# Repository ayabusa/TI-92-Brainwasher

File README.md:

# TI-92 Brainwasher
Welcome to the Brainwasher repo ! Here you'll find everything you need, to create and use a custom ROM module for your TI-92.

## Why this project ?
This project aims to recreate the original ROM module from the TI-92 and add the ability to change the OS on it. Indeed the original ROM module is readonly (unless you want to blast UV on it...), so once you bought the calc, you can't ever update :( 

Another use case is repairability, if the module was lost or damaged, the calc became useless. 

But not anymore with this project you can recreate your own and tweak the OS to your liking !

## Great, how do I get this stuff
This project is centered around two boards, a module board (Brainswap) containing 2 EEPROM that will go into the calc. And a programmer (Brainwasher) that will enable you to change the OS of the module.

There are multiple steps needed, you'll need to build the hardware, flash the firmware and finally use the PC software app.

### Hardware
First you'll need to gather the following components, AliExpress is your friend:
- `1x STM32F103C8T6 Bluepill` board, I recommend the `Blupill plus` from WeAct Studio
- `1x ST-Link`, these come in different form factor, there is often a bundle version containing one with the Bluepill
- `3x SN74HC595N` register shift
- `2x Male header 2.0mm with 2x13P or 2x12P or 2x11P`, there is 2 collumn not connected on each connector so buy what is the cheapest
- `2x SST39SF040 in TSOP32` EEPROM
- `2x SMD Female socket 2.0mm in 2x13P or 2x12P or 2x11P`
- `5x 100nF Capacitor in 1206 SMD`
- `2x 10µF Capacitor in 1206 SMD`
- `3x 10k Resistor in 1206 SMD`

On top of that you'll need to order the two custom PCB (more info in `pcb/README.txt`) using an online service like [PCBWay](https://www.pcbway.com/)

Once you have everything, solder everything according to the silkscreen markings on the PCB and using reference images. Be really carefull at the orientation of the components.
- The Bluepill orientation is clearly indicated by the silkscreen.
- The 74HC595 orientation is indicated by the semi-circle on the silkscreen and present on the actual ICs.
- The SST39SF040 orientation is indicated by the little dot in the corner of the silkscreen, also present on the actual ICs.
- For the male/female connector, if you got a 2x11P or 2x12P, you'll need to place the pins to the opposite of the NC ones

#### Reference pictures

### Firmware
Once everything is assembled, you we'll need to program the Bluepill with the firmware located in the `firmware` directory you'll find more info in `firmware/README.txt`.

### Software
Then you'll be able to flash a ROM onto your custom module using the PC software, you can find more info in `software/README.txt`.

### Replacing the module
Once everything else is done you can put your module in the calc by opening it's back.

BE CAREFUL !!! REMOVE ALL THE BATTERIES FIRST !!!

### Box
There is also a purely cosmetic packaging I made, inspired by the original TI-92 Box. You can print it using the pdf in `box/box.pdf`

## License
There are different part in this project, and different Licenses, refer to the LICENSE.txt in each folder. If unsure contact me via Email at `contact [at] ayabusa (dot) dev`

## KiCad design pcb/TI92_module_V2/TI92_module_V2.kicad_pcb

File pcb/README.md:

# Custom TI-92 Module PCB
This section of the repo contains the schematic and PCB for the two different boards. You can use the `.zip` files in the gerber directory to order them on different websites.

## Ordering from PCBWay
If you want to support me you can order the PCB directly from PCBWay using these links

### Brainswap module

### Brainwasher board

## How to edit
These files were created using KiCad 10.0, you can edit them using this software.

## License
This part of the repo is licensed under the CC BY-NC-SA 4.0 license, see more details in the LICENSE.txt file

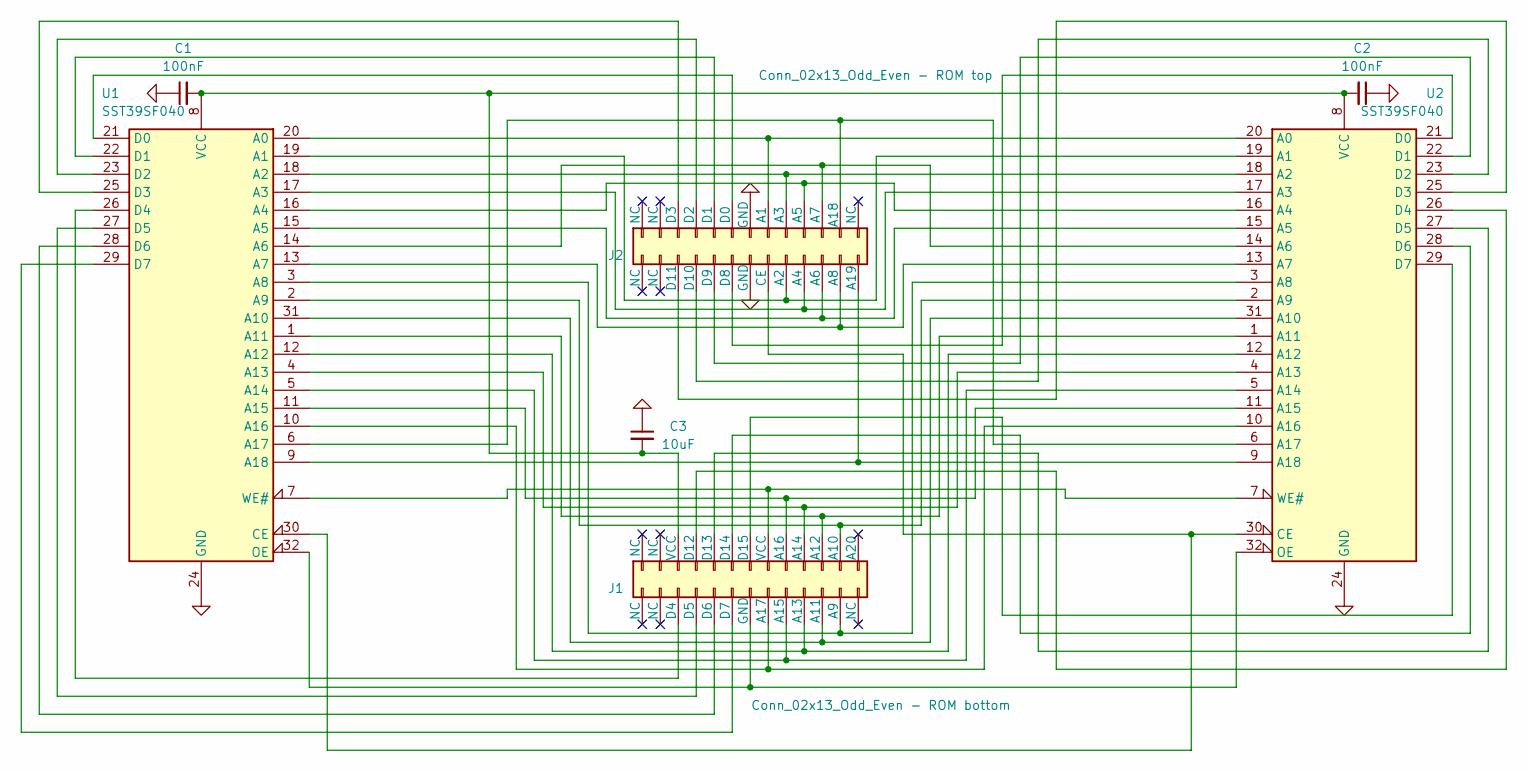
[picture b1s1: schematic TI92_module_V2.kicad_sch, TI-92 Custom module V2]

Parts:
C1, C2: 100nF; C_1206_3216Metric_Pad1.33x1.80mm_HandSolder
C3: 10uF; C_1206_3216Metric_Pad1.33x1.80mm_HandSolder
J1: Conn_02x13_Odd_Even - ROM bottom; PinSocket_2x13_P2.00mm_Vertical_SMD
J2: Conn_02x13_Odd_Even - ROM top; PinSocket_2x13_P2.00mm_Vertical_SMD
U1, U2: SST39SF040; SOP50P1400X120-32N

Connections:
GND: C1.1, C2.1, C3.1, J2.13 (GND), J2.14 (GND), U1.24 (GND), U2.24 (GND)
unnamed: J1.24 (A9), U1.3 (A8), U2.3 (A8)
unnamed: J1.23 (A10), U1.2 (A9), U2.2 (A9)
unnamed: J1.22 (A11), U1.31 (A10), U2.31 (A10)
unnamed: J1.21 (A12), U1.1 (A11), U2.1 (A11)
unnamed: J1.20 (A13), U1.12 (A12), U2.12 (A12)
unnamed: J1.19 (A14), U1.4 (A13), U2.4 (A13)
unnamed: J1.18 (A15), U1.5 (A14), U2.5 (A14)
unnamed: J1.17 (A16), U1.11 (A15), U2.11 (A15)
unnamed: J1.16 (A17), U1.10 (A16), U2.10 (A16)
unnamed: J1.6 (D4), U1.26 (D4)
unnamed: J1.8 (D5), U1.27 (D5)
unnamed: J1.10 (D6), U1.28 (D6)
unnamed: J1.12 (D7), U1.29 (D7)
unnamed: J1.7 (D12), U2.26 (D4)
unnamed: J1.9 (D13), U2.27 (D5)
unnamed: J1.11 (D14), U2.28 (D6)
unnamed: J1.13 (D15), U2.29 (D7)
unnamed: J1.14 (GND), U1.32 (OE), U2.32 (OE)
unnamed: J2.15 (A1), U1.20 (A0), U2.20 (A0)
unnamed: J2.18 (A2), U1.19 (A1), U2.19 (A1)
unnamed: J2.17 (A3), U1.18 (A2), U2.18 (A2)
unnamed: J2.20 (A4), U1.17 (A3), U2.17 (A3)
unnamed: J2.19 (A5), U1.16 (A4), U2.16 (A4)
unnamed: J2.22 (A6), U1.15 (A5), U2.15 (A5)
unnamed: J2.21 (A7), U1.14 (A6), U2.14 (A6)
unnamed: J2.24 (A8), U1.13 (A7), U2.13 (A7)
unnamed: J2.23 (A18), U1.6 (A17), U2.6 (A17)
unnamed: J2.26 (A19), U1.9 (A18), U2.9 (A18)
unnamed: J2.16 (CE), U1.30 (CE), U2.30 (CE)
unnamed: J2.11 (D0), U1.21 (D0)
unnamed: J2.9 (D1), U1.22 (D1)
unnamed: J2.7 (D2), U1.23 (D2)
unnamed: J2.5 (D3), U1.25 (D3)
unnamed: J2.12 (D8), U2.21 (D0)
unnamed: J2.10 (D9), U2.22 (D1)
unnamed: J2.8 (D10), U2.23 (D2)
unnamed: J2.6 (D11), U2.25 (D3)
unnamed: C1.2, C2.2, C3.2, J1.5 (VCC), U1.8 (VCC), U2.8 (VCC)
unnamed: J1.15 (VCC), U1.7 (WE#), U2.7 (WE#)

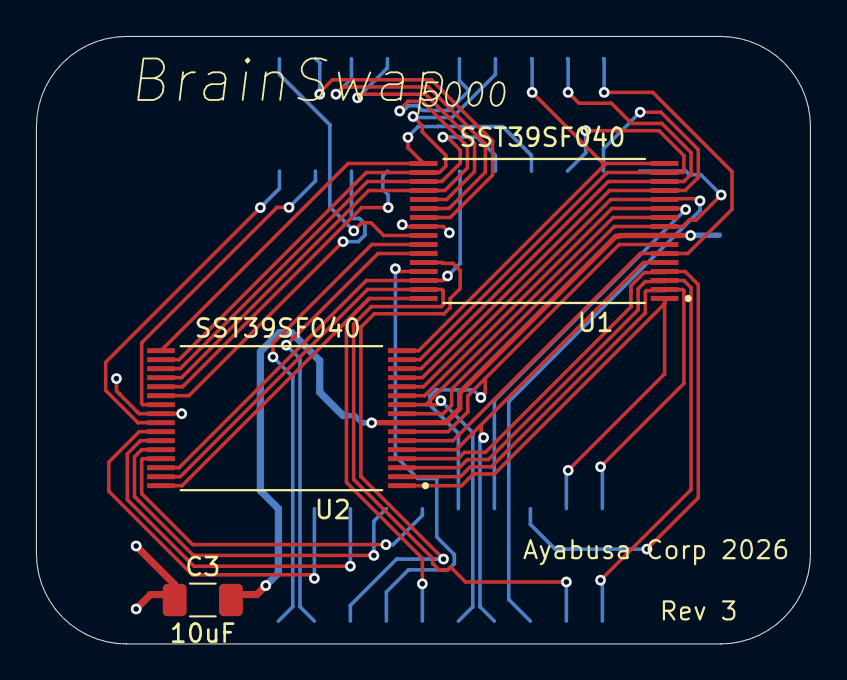
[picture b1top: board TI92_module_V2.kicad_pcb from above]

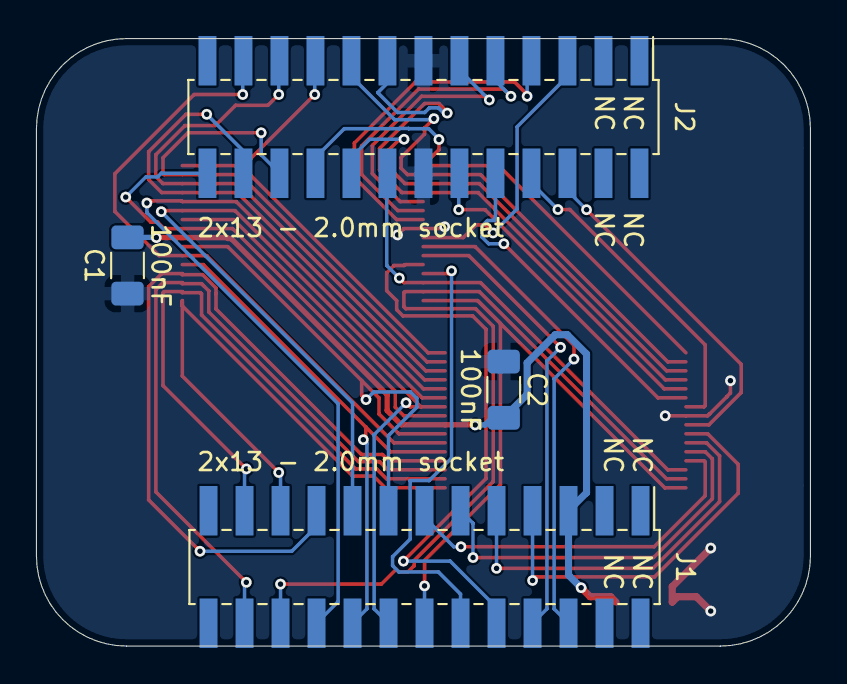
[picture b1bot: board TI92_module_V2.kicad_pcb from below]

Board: 2 copper layers, 43.0 x 33.8 mm, 7 parts (4 on the bottom side), 40 nets.

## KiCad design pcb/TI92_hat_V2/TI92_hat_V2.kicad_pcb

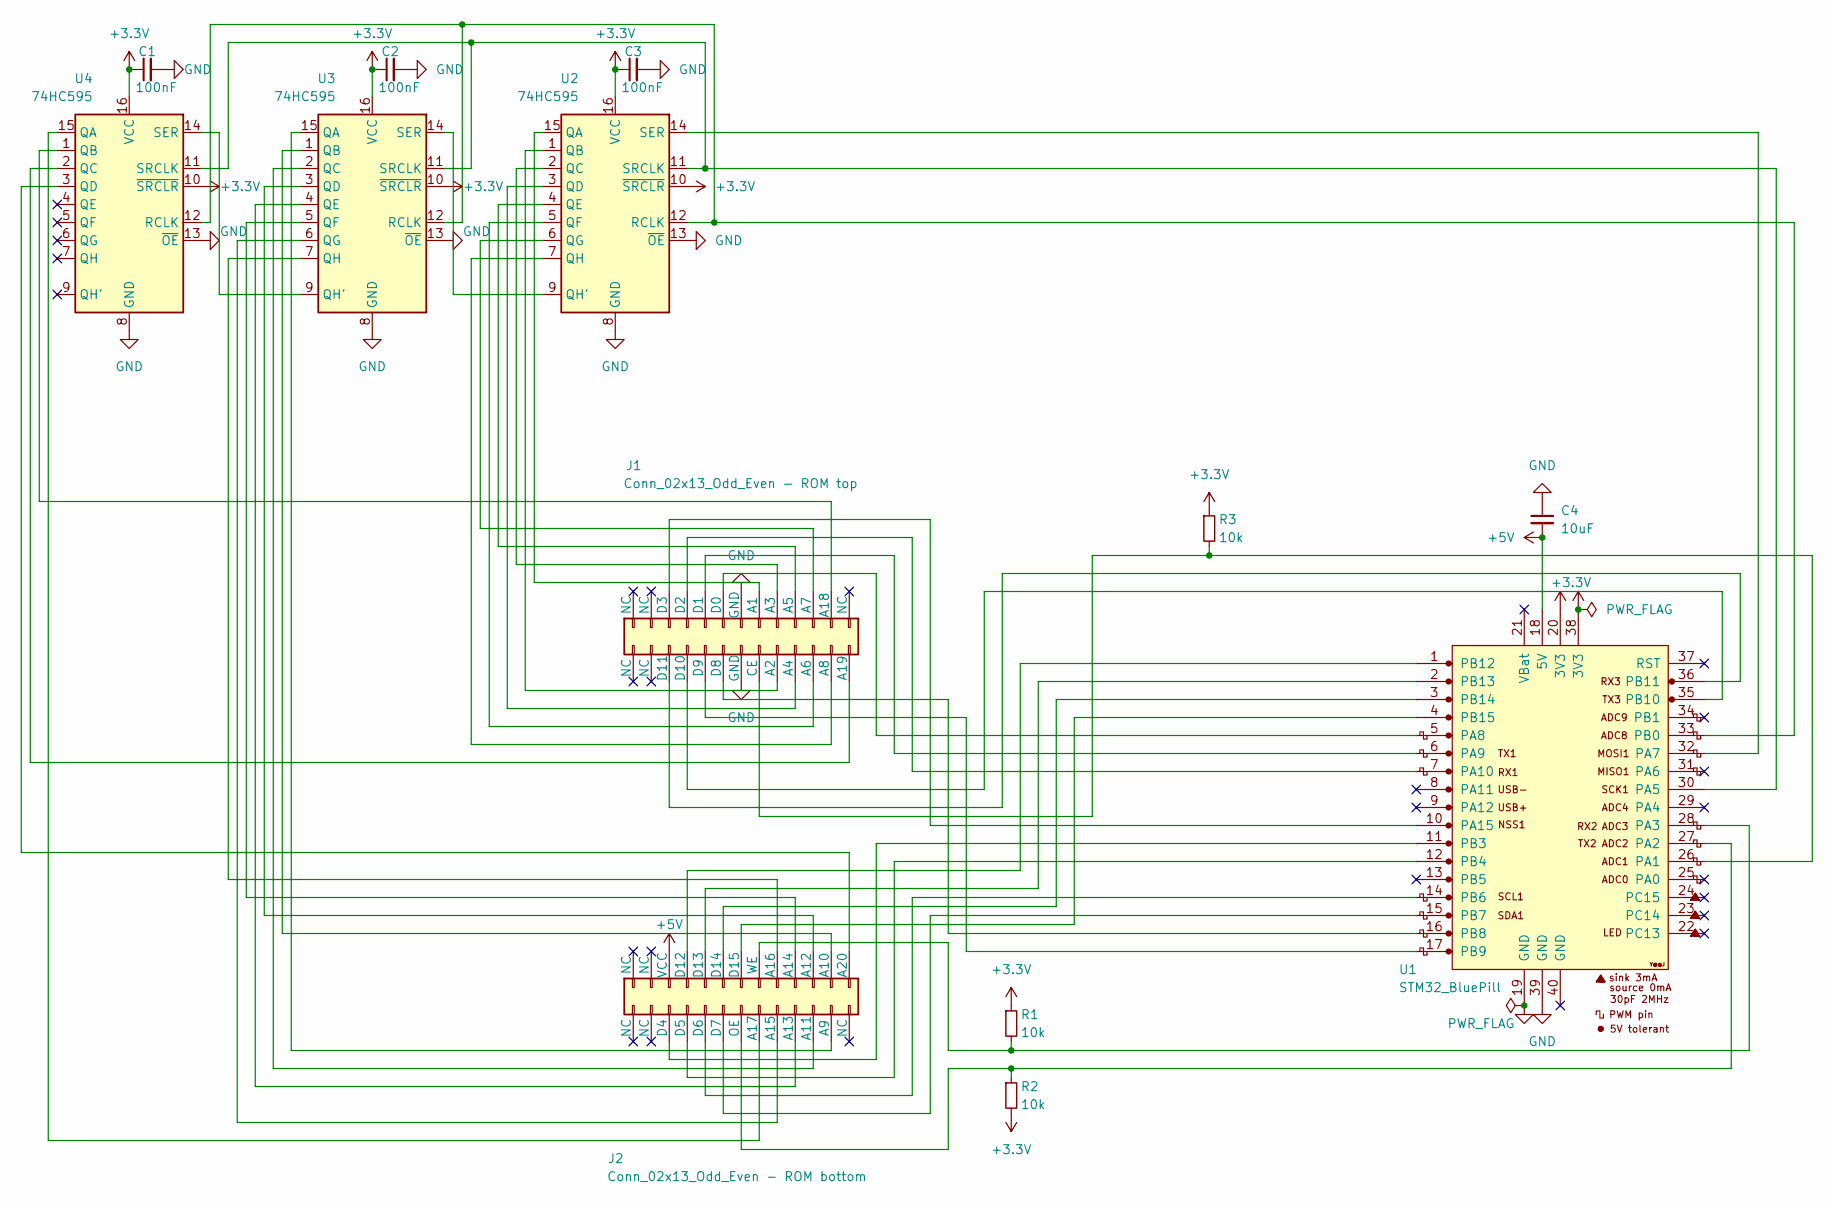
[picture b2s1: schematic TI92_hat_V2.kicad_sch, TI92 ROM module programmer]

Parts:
C1, C2, C3: 100nF; C_1206_3216Metric_Pad1.33x1.80mm_HandSolder
C4: 10uF; C_1206_3216Metric_Pad1.33x1.80mm_HandSolder
J1: Conn_02x13_Odd_Even - ROM top; PinHeader_2x13_P2.00mm_Vertical
J2: Conn_02x13_Odd_Even - ROM bottom; PinHeader_2x13_P2.00mm_Vertical
R1, R2, R3: 10k; R_1206_3216Metric_Pad1.30x1.75mm_HandSolder
U1: STM32_BluePill; YAAJ_BluePill_1
U2, U3, U4: 74HC595; DIP-16_W7.62mm_LongPads

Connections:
+3.3V: C1.1, C2.1, C3.1, R1.1, R2.2, R3.1, U1.20 (3V3), U1.38 (3V3), U2.10 (~SRCLR), U2.16 (VCC), U3.10 (~SRCLR), U3.16 (VCC), U4.10 (~SRCLR), U4.16 (VCC)
+5V: C4.2, J2.5 (VCC), U1.18 (5V)
GND: C1.2, C2.2, C3.2, C4.1, J1.13 (GND), J1.14 (GND), U1.19 (GND), U1.39 (GND), U2.8 (GND), U2.13 (~OE), U3.8 (GND), U3.13 (~OE), U4.8 (GND), U4.13 (~OE)
unnamed: J1.15 (A1), U2.15 (QA)
unnamed: J1.18 (A2), U2.1 (QB)
unnamed: J1.17 (A3), U2.2 (QC)
unnamed: J1.20 (A4), U2.3 (QD)
unnamed: J1.19 (A5), U2.4 (QE)
unnamed: J1.22 (A6), U2.5 (QF)
unnamed: J1.21 (A7), U2.6 (QG)
unnamed: J1.24 (A8), U2.7 (QH)
unnamed: J1.23 (A18), U4.1 (QB)
unnamed: J1.26 (A19), U4.2 (QC)
unnamed: J1.16 (CE), R3.2, U1.26 (PA1)
unnamed: J1.11 (D0), U1.5 (PA8)
unnamed: J1.9 (D1), U1.6 (PA9)
unnamed: J1.7 (D2), U1.7 (PA10)
unnamed: J1.5 (D3), U1.10 (PA15)
unnamed: J1.12 (D8), U1.16 (PB8)
unnamed: J1.10 (D9), U1.17 (PB9)
unnamed: J1.8 (D10), U1.35 (PB10)
unnamed: J1.6 (D11), U1.36 (PB11)
unnamed: J2.24 (A9), U3.15 (QA)
unnamed: J2.23 (A10), U3.1 (QB)
unnamed: J2.22 (A11), U3.2 (QC)
unnamed: J2.21 (A12), U3.3 (QD)
unnamed: J2.20 (A13), U3.4 (QE)
unnamed: J2.19 (A14), U3.5 (QF)
unnamed: J2.18 (A15), U3.6 (QG)
unnamed: J2.17 (A16), U3.7 (QH)
unnamed: J2.16 (A17), U4.15 (QA)
unnamed: J2.25 (A20), U4.3 (QD)
unnamed: J2.6 (D4), U1.11 (PB3)
unnamed: J2.8 (D5), U1.12 (PB4)
unnamed: J2.10 (D6), U1.14 (PB6)
unnamed: J2.12 (D7), U1.15 (PB7)
unnamed: J2.7 (D12), U1.1 (PB12)
unnamed: J2.9 (D13), U1.2 (PB13)
unnamed: J2.11 (D14), U1.3 (PB14)
unnamed: J2.13 (D15), U1.4 (PB15)
unnamed: J2.14 (OE), R2.1, U1.27 (PA2)
unnamed: J2.15 (WE), R1.2, U1.28 (PA3)
unnamed: U1.30 (PA5), U2.11 (SRCLK), U3.11 (SRCLK), U4.11 (SRCLK)
unnamed: U1.32 (PA7), U2.14 (SER)
unnamed: U1.33 (PB0), U2.12 (RCLK), U3.12 (RCLK), U4.12 (RCLK)
unnamed: U2.9 (QH'), U3.14 (SER)
unnamed: U3.9 (QH'), U4.14 (SER)

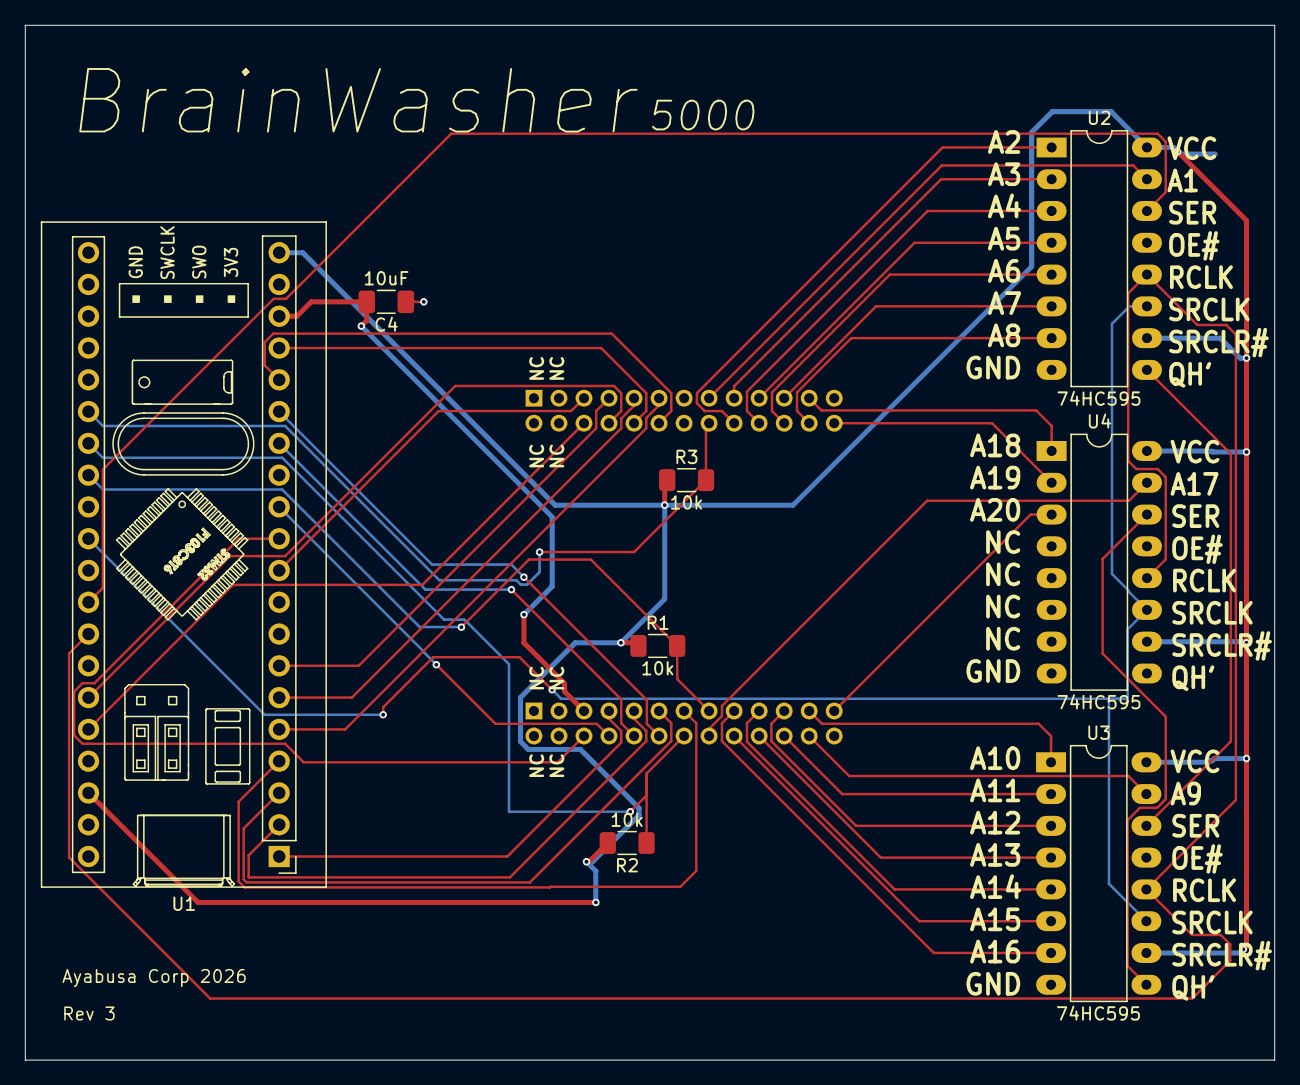
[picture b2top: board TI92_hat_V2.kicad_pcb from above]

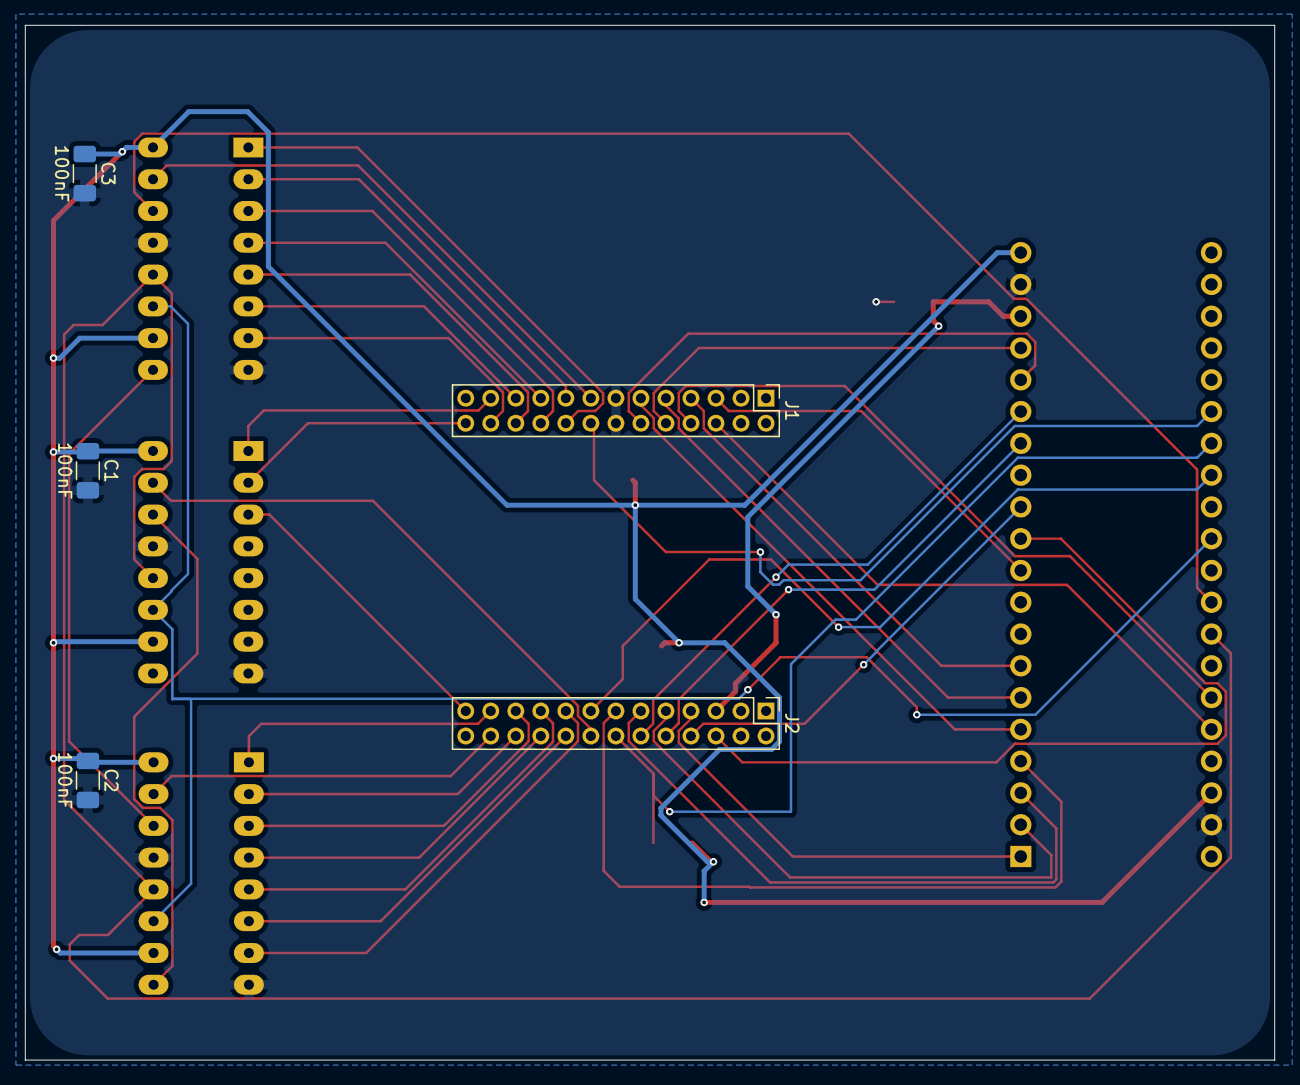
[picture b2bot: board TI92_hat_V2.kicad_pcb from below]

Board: 2 copper layers, 99.8 x 82.7 mm, 13 parts (5 on the bottom side), 47 nets.
